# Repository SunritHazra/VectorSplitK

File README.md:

# VectorSplitK

An open-source, wireless, high-profile 42-key mechanical split keyboard. Built around the powerful Seeed Studio XIAO nRF52840, the VectorSplitK features an aggressive columnar stagger, custom-modeled flat profile keycaps, and a robust dual-case mechanical assembly. This project is my first split keyboard. The PCB was made entirely in KiCad and the CAD was done in Autodesk Fusion.

> Full day-by-day design log, decisions, and dead ends: [JOURNAL.md](./JOURNAL.md)

**Project stats:** 14 build-log days · ~40h 20m total design time · 100% designing progress, 0% building progress (as of the latest journal entry)

**On the name:** Follows the author's personal naming convention for electronics projects (used previously for *hackpad* and *devboard*) — a descriptive word, a short form of the project's defining trait ("Split"), and a single trailing letter — giving **VectorSplitK**.

---

## Renders

### Standard Top View

### Isometric Split Profile

### Rear Profile (USB-C & Alignment)

---

## Hardware Architecture

### 1. Electrical Schematic

The electrical system uses hierarchical sheets in KiCad to define identical left and right sides. It resolves typical multi-sheet duplicate ground issues by utilizing sheet-specific power flags (${SHEETNAME}_GND).

Main Sheet

Left Half Matrix

Right Half Matrix

### 2. Footprints

- **Switch Footprints:** High-profile `acheron_MXH:MX100H` (1.00u) and `acheron_MXH:MX150H` (1.50u) hotswap-ready switches (42 total, 21 per side).
- **Diodes:** `Diode_SMD:D_SOD-123` (42 total, 1 per key).
- **Mounting Holes:** `MountingHole:MountingHole_3.2mm_M3_DIN965_Pad` (8 total, 4 per side).
- **Resistors:** `Resistor_SMD:R_0805_2012Metric` (4 total, 2 per side).
- **Integrated Circuit:** `modified-XIAO-nRF52840-SMD:modified-XIAO-nRF52840-SMD` (2 total, 1 per side).
- **Testing Points:** `TestPoint:TestPoint_Pad_D2.0mm` (4 total, 2 per side).
- **Mousebites:** Clean PCB snapping using `PCM_marbastlib-various:mousebites_5p5mm_easysnap` (3 break-offs).

### 3. Printed Circuit Board Assembly

Designed for rugged reliability and high-profile ergonomics using the custom footprints above.

KiCad PCB Window

KiCad PCB Render

KiCad PCBA Render

KiCad PCB Back Side

KiCad PCBA Back Side

- **Design files:** [`/PCBA`](./PCBA)

### 4. Enclosure & CAD Assembly

Designed from scratch in Autodesk Fusion, featuring integrated battery slots, precise USB-C ports, and secure brass threaded insert sockets.

file structure of fusion

top case and bottom case together in fusion

section analysis in fusion showing the screw assembly

- **Tolerance Offset:** 0.2 mm case-on-case fit alignment.
- **Plates:** Structural upper case acts as a switch plate, anchoring switches securely.
- **Keycaps:** Custom-modeled 1.00u and 1.50u flat profile MX-stem keycaps tailored for 3D printing.
- **CAD files:** [`/CAD`](./CAD)

---

## Libraries & References

**KiCad libraries used:**
- [mito-keyboard](https://github.com/mito-keyboard/sito-simplified/tree/sain) — base keyboard library
- [marbastlib](https://github.com/ebastler/marbastlib) — mousebite & hardware footprints
- [Panelization](https://github.com/madworm/Panelization.pretty) — panelization footprints
- [Seeed XIAO KiCad Library](https://github.com/Seeed-Studio/OPL_Kicad_Library/blob/master/XIAO%20Family/XIAO.kicad_sch) — XIAO nRF52840 schematic symbol

**Layout & edge-cut inspiration** (referenced for switch arrangement and board outline conventions):
- [mito-keyboard](https://github.com/mito-keyboard/mito-simplified/tree/main)
- [TaoTeChing](https://github.com/sudo-apt-install-tap/TaoTeChing)
- [OVERRIDE-X3D-Split-Keeb](https://github.com/DevX-Dragon/OVERRIDE-X3D-Split-Keeb)

**Keycap reference model:** [Flat MX Keycaps — Printables](https://www.printables.com/model/467351-flat-mx-keycaps), used as a base to project and re-model custom 1.00u/1.50u profiles.

---

## Design Notes

**Columnar stagger layout:** Switches placed on a 20 mm grid; second and fourth rows shifted 10 mm up, the middle row shifted 20 mm up, with board edges drawn 5 mm out from the outermost keys.

**Hierarchical sheet grounding:** KiCad hierarchical sheets duplicate net names by default, which merged the left/right ground nets into one. Fixed using sheet-specific power flags (`${SHEETNAME}_GND`), producing distinct `Left_GND` and `Right_GND` nets per half.

**Case construction (Fusion 360):** Built symmetrically — one side of the PCB modeled, then mirrored — with:
- Screw hubs extruded directly from the PCB's mounting hole positions
- A battery cavity sized to the WLY394058 LiPo and centered relative to the four mounting screws
- A USB-C cutout on the lower case wall, offset slightly oversized for clearance

**Keycap modeling:** 1.00u caps built by lofting projected upper/lower faces of a reference keycap, then hollowing and adding a stem + cross-hub. 1.50u caps were derived by splitting the 1.00u shape, spacing the halves 9 mm apart, and bridging the gap. Stem geometry was verified by cutting the actual switch stem shape directly into the keycap model to guarantee fit.

**Upper case (switch plate):** Modeled by projecting all switch bodies into a sketch, offsetting 1 mm around each switch and 1.5 mm along the walls, then extruding to the wall thickness (4.05 mm) with screw-hole pillars extended up from the PCB. Outer walls were thinned via a −0.8 mm facial offset on the curved edges for a lighter profile. Corner/cutout dimensions (14.70 × 14.70 mm switch openings, 0.705 mm corner radius) were carried over from the author's earlier hackpad build.

**Design refinements:** The SoC position, PCB mounting holes, and upper-case mounting holes were all iterated to (1) clear the USB-C cable path symmetrically on both halves, (2) keep mounting holes equidistant from the three nearest switches for insert clearance, and (3) keep the upper-case screw geometry in sync with the final PCB layout.

---

## Fabrication & Testing

- **Electrical Rule Check (ERC)** run after schematic completion to catch connection errors before layout.
- **Design Rule Check (DRC)** run after routing, with remaining clearance/edge errors resolved before export.
- **Silkscreen:** Front Fab and Back Fab converted to Back Silkscreen; User.Drawings converted to Front Silkscreen and User.Eco1 to Back Silkscreen; testing points manually labeled and text centered relative to switches. Author name, project name, and build month/year added to the front silkscreen for the final revision.
- **Gerber export:** Full fabrication output exported as `VectorSplitK_Gerber.zip`.
- **Fab test:** Gerbers test-uploaded to JLCPCB to validate manufacturability ahead of ordering.
- **STEP export:** PCB exported at multiple levels of detail (full detail for reference, minimal/simplified for clean CAD import) to support Fusion 360 case modeling.

---

## Bill of Materials (BOM)

Full sourcing sheet with vendors and pricing: [`/Bill of Materials`](<./Bill of Materials>)

### Electronics & PCBs

- **2x** PCBs (Left & Right snap-apart panels)
- **2x** Seeed Studio XIAO nRF52840 MCU boards
- **2x** WLY394058 3.7V 1000mAh 1S LiPo Batteries (3.9 mm thickness for slim fit)
- **42x** Mechanical switches (MX compatible)
- **42x** Kailh MX Hotswap Sockets
- **42x** SOD-123 SMD Diodes (`1N4148`)
- **4x** `0805` Metric SMD Resistors (2 per side)

### Hardware & Case Assembly

- **M3** Screws (Specific lengths to clamp top and bottom cases)
- **M3** Brass Knurled Heat-Staking Inserts (Pressed into bottom case pillars)
- **1x Set** Custom-printed 1.00u & 1.50u flat keycaps (STEP files included)

### Sourcing

| Component | Vendor |
|---|---|
| PCB Fabrication | JLCPCB |
| Switches & Kailh Hotswap Sockets | Meckeys |
| Diodes, Resistors, SoC, Battery | Robu.in |
| Screws & Knurled Inserts | OnlyScrews |

---

## Firmware

The board runs wireless **ZMK** firmware on the **XIAO nRF52840**, using a custom shield built on the upstream `seeeduino_xiao_ble` board support.

### Matrix

5 columns × 5 rows per half (21 keys/side, 42 total — a 4×5 grid plus 1 thumb key), with `diode-direction = "col2row"` matching the SOD-123 diode orientation on the PCB.

| Signal | XIAO Pin |
|---|---|
| COL_0 | P0.03 |
| COL_1 | P0.28 |
| COL_2 | P0.29 |
| COL_3 | P0.04 |
| COL_4 | P0.05 |
| ROW_0 | P1.15 |
| ROW_1 | P1.14 |
| ROW_2 | P1.13 |
| ROW_3 | P1.12 |
| ROW_4 | P1.11 |

### Config

Firmware lives in [`/zmk-config`](./zmk-config), structured as its own ZMK user-config repo:
zmk-config/
├── build.yaml
├── config/
│   ├── vectorsplitk.keymap
│   ├── vectorsplitk.conf
│   └── west.yml
├── boards/shields/vectorsplitk/
│   ├── vectorsplitk.dtsi
│   ├── vectorsplitk_left.overlay
│   ├── vectorsplitk_right.overlay
│   ├── vectorsplitk.zmk.yml
│   ├── Kconfig.shield
│   └── Kconfig.defconfig
└── .github/workflows/build.yml

Pushing this folder as its own GitHub repo triggers a GitHub Actions build via `build.yaml`, producing `vectorsplitk_left-seeeduino_xiao_ble-zmk.uf2` and `vectorsplitk_right-seeeduino_xiao_ble-zmk.uf2` under the Actions tab, no local toolchain required.

> **Known caveat:** the matrix transform assumes COL_0 is the innermost column (closest to the thumb key) on both halves. If keys type in mirrored left-right order on first flash, reverse the column order in `vectorsplitk.dtsi` — a firmware-only fix, no rewiring needed.

### Flashing

1. Double-tap Reset on the XIAO nRF52840 to mount it as a USB drive.
2. Drag the matching `.uf2` (left or right) onto the drive.

---

## AI as a Design Collaborator

While the hardware engineering, PCB routing, firmware architecture, and 3D CAD modeling were completed manually, AI (Gemini, ChatGPT, and Claude) was used as a technical assistant throughout the project—not to generate designs, but to help research, troubleshoot, validate decisions, and improve documentation.

- **Brainstorming:** Helped refine the project name (**VectorSplitK**).
- **Research & Validation:** Verified switch footprints, component choices, and battery selection.
- **Debugging:** Assisted in resolving KiCad schematic and hierarchical-sheet issues.
- **Design Review:** Discussed engineering trade-offs, BOM costs, and manufacturing decisions.
- **Firmware & Documentation:** Helped architect the initial ZMK firmware configuration, reviewed the PCB matrix for firmware setup, and improved the project's technical documentation.

> **Project Integrity:** All schematics, PCB layouts, routing, CAD models, and mechanical design were created manually in KiCad and Autodesk Fusion. AI was used only for research, troubleshooting, review, firmware guidance, and documentation.

---

## License

This project is licensed under the MIT License - see the [LICENSE](./LICENSE) file for details.

---

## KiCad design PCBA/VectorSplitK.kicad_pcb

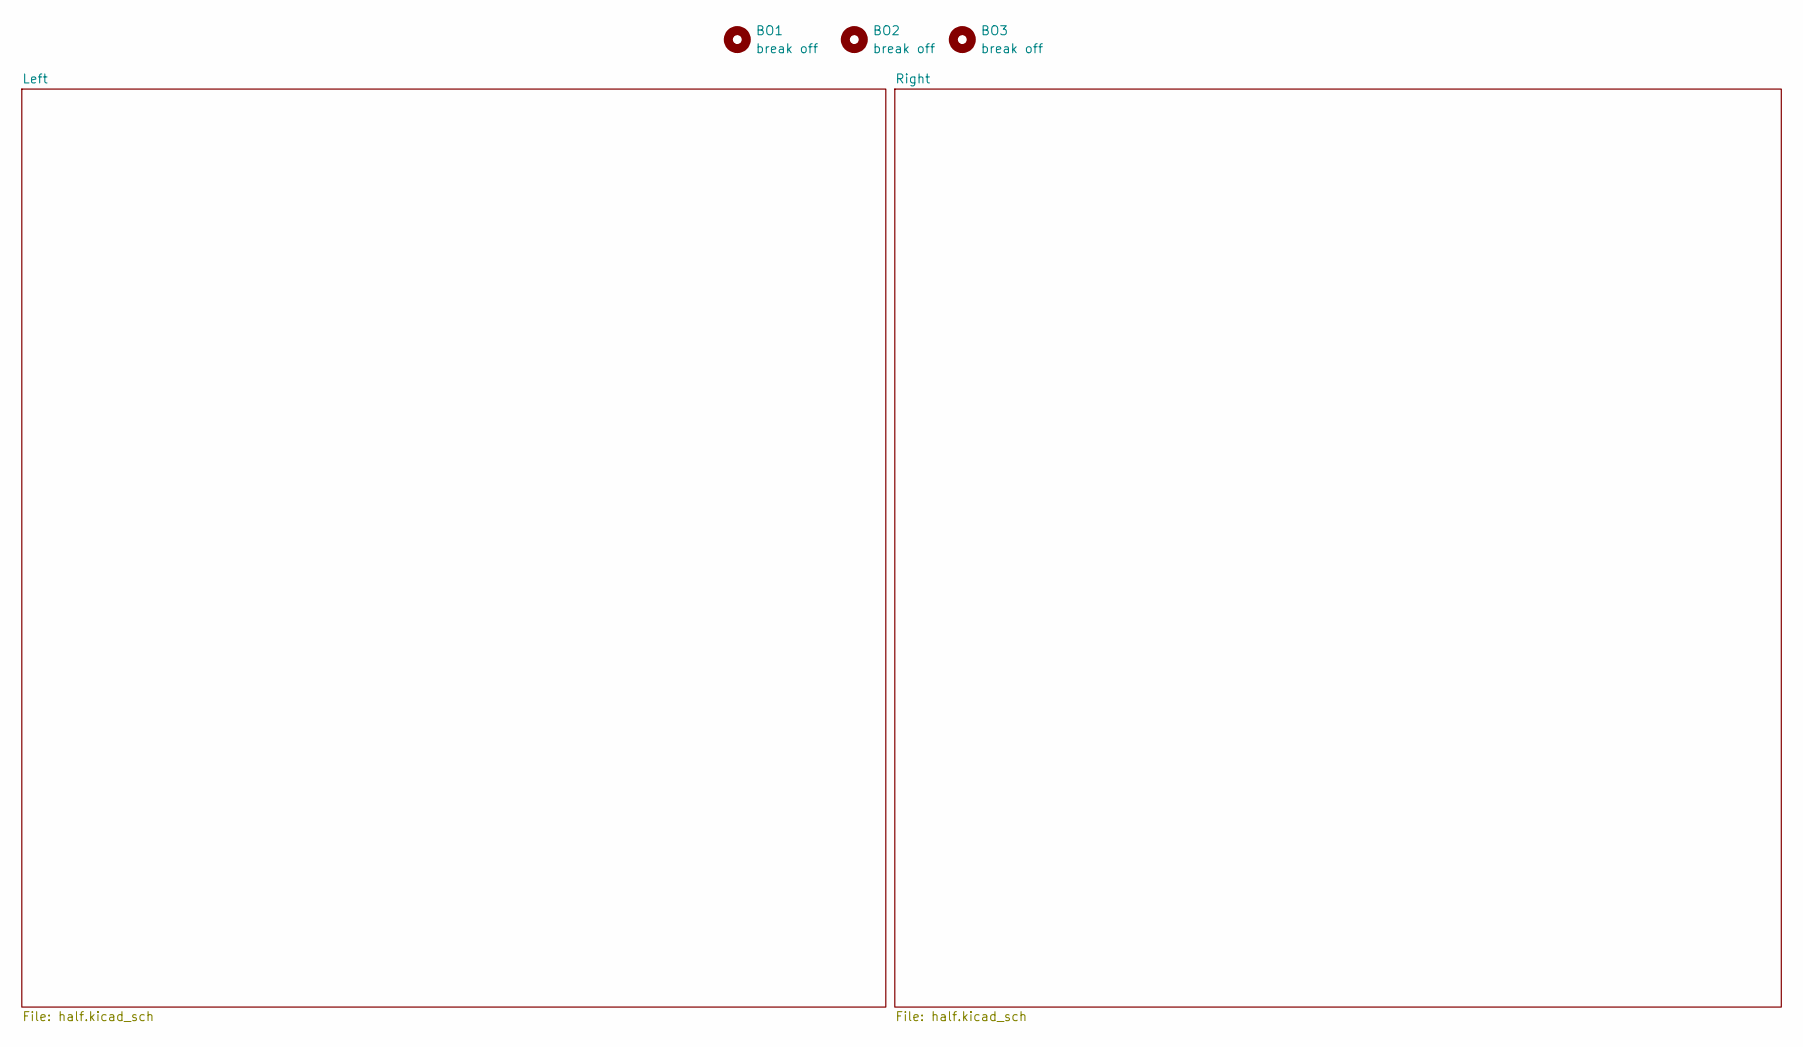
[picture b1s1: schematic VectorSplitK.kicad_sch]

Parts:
BO1, BO2, BO3: break off; mouse-bite-2mm-slot

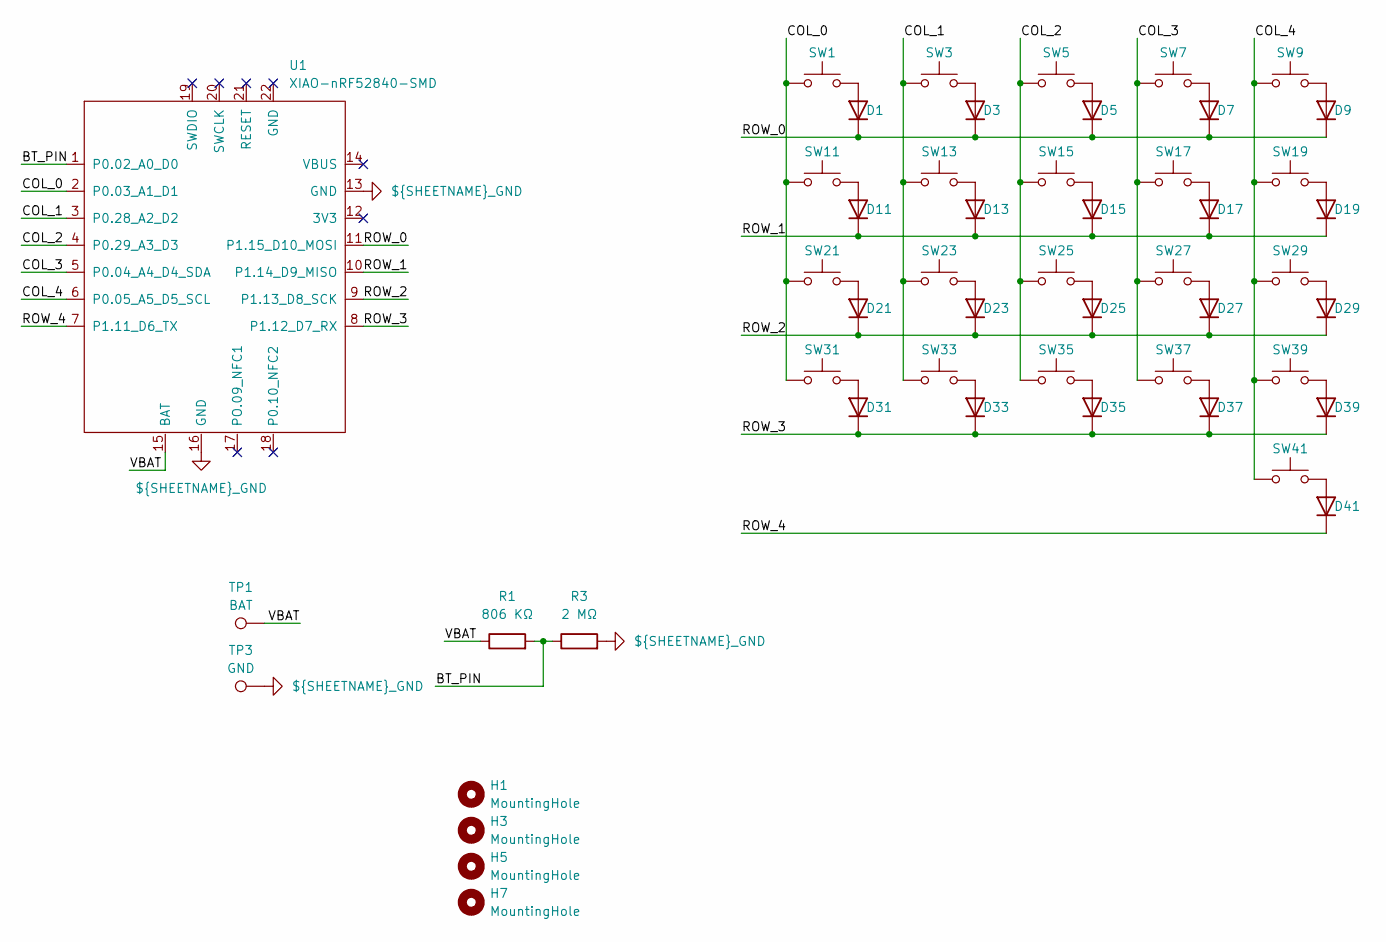
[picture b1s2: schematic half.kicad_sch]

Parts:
D1, D3, D5, D7, D9, D11, D13, D15, D17, D19, D21, D23, D25, D27, D29, D31, D33, D35, D37, D39, D41: D; D_SOD-123
H1, H3, H5, H7: MountingHole; MountingHole_3.2mm_M3_DIN965_Pad
R1: 806 KΩ; R_0805_2012Metric
R3: 2 MΩ; R_0805_2012Metric
SW1, SW3, SW5, SW7, SW9, SW11, SW13, SW15, SW17, SW19, SW21, SW23, SW25, SW27, SW29, SW31, SW33, SW35, SW37, SW39: SW_Push; MX100H
SW41: SW_Push; MX150H
TP1: BAT; TestPoint_Pad_D2.0mm
TP3: GND; TestPoint_Pad_D2.0mm
U1: XIAO-nRF52840-SMD; modified-XIAO-nRF52840-SMD

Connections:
/Left/BT_PIN: R1.2, R3.1, U1.1 (P0.02_A0_D0)
/Left/COL_0: SW1.1, SW11.1, SW21.1, SW31.1, U1.2 (P0.03_A1_D1)
/Left/COL_1: SW3.1, SW13.1, SW23.1, SW33.1, U1.3 (P0.28_A2_D2)
/Left/COL_2: SW5.1, SW15.1, SW25.1, SW35.1, U1.4 (P0.29_A3_D3)
/Left/COL_3: SW7.1, SW17.1, SW27.1, SW37.1, U1.5 (P0.04_A4_D4_SDA)
/Left/COL_4: SW9.1, SW19.1, SW29.1, SW39.1, SW41.1, U1.6 (P0.05_A5_D5_SCL)
/Left/ROW_0: D1.1 (K), D3.1 (K), D5.1 (K), D7.1 (K), D9.1 (K), U1.11 (P1.15_D10_MOSI)
/Left/ROW_1: D11.1 (K), D13.1 (K), D15.1 (K), D17.1 (K), D19.1 (K), U1.10 (P1.14_D9_MISO)
/Left/ROW_2: D21.1 (K), D23.1 (K), D25.1 (K), D27.1 (K), D29.1 (K), U1.9 (P1.13_D8_SCK)
/Left/ROW_3: D31.1 (K), D33.1 (K), D35.1 (K), D37.1 (K), D39.1 (K), U1.8 (P1.12_D7_RX)
/Left/ROW_4: D41.1 (K), U1.7 (P1.11_D6_TX)
/Left/VBAT: R1.1, TP1.1, U1.15 (BAT)
Left_GND: R3.2, TP3.1, U1.13 (GND), U1.16 (GND)
unnamed: D1.2 (A), SW1.2
unnamed: D3.2 (A), SW3.2
unnamed: D5.2 (A), SW5.2
unnamed: D7.2 (A), SW7.2
unnamed: D9.2 (A), SW9.2
unnamed: D11.2 (A), SW11.2
unnamed: D13.2 (A), SW13.2
unnamed: D15.2 (A), SW15.2
unnamed: D17.2 (A), SW17.2
unnamed: D19.2 (A), SW19.2
unnamed: D21.2 (A), SW21.2
unnamed: D23.2 (A), SW23.2
unnamed: D25.2 (A), SW25.2
unnamed: D27.2 (A), SW27.2
unnamed: D29.2 (A), SW29.2
unnamed: D31.2 (A), SW31.2
unnamed: D33.2 (A), SW33.2
unnamed: D35.2 (A), SW35.2
unnamed: D37.2 (A), SW37.2
unnamed: D39.2 (A), SW39.2
unnamed: D41.2 (A), SW41.2

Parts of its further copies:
D2, D4, D6, D8, D10, D12, D14, D16, D18, D20, D22, D24, D26, D28, D30, D32, D34, D36, D38, D40, D42: D; D_SOD-123
H2, H4, H6, H8: MountingHole; MountingHole_3.2mm_M3_DIN965_Pad
R2: 806 KΩ; R_0805_2012Metric
R4: 2 MΩ; R_0805_2012Metric
SW2, SW4, SW6, SW8, SW10, SW12, SW14, SW16, SW18, SW20, SW22, SW24, SW26, SW28, SW30, SW32, SW34, SW36, SW38, SW40: SW_Push; MX100H
SW42: SW_Push; MX150H
TP2: BAT; TestPoint_Pad_D2.0mm
TP4: GND; TestPoint_Pad_D2.0mm
U2: XIAO-nRF52840-SMD; modified-XIAO-nRF52840-SMD

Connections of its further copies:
/Right/BT_PIN: R2.2, R4.1, U2.1 (P0.02_A0_D0)
/Right/COL_0: SW2.1, SW12.1, SW22.1, SW32.1, U2.2 (P0.03_A1_D1)
/Right/COL_1: SW4.1, SW14.1, SW24.1, SW34.1, U2.3 (P0.28_A2_D2)
/Right/COL_2: SW6.1, SW16.1, SW26.1, SW36.1, U2.4 (P0.29_A3_D3)
/Right/COL_3: SW8.1, SW18.1, SW28.1, SW38.1, U2.5 (P0.04_A4_D4_SDA)
/Right/COL_4: SW10.1, SW20.1, SW30.1, SW40.1, SW42.1, U2.6 (P0.05_A5_D5_SCL)
/Right/ROW_0: D2.1 (K), D4.1 (K), D6.1 (K), D8.1 (K), D10.1 (K), U2.11 (P1.15_D10_MOSI)
/Right/ROW_1: D12.1 (K), D14.1 (K), D16.1 (K), D18.1 (K), D20.1 (K), U2.10 (P1.14_D9_MISO)
/Right/ROW_2: D22.1 (K), D24.1 (K), D26.1 (K), D28.1 (K), D30.1 (K), U2.9 (P1.13_D8_SCK)
/Right/ROW_3: D32.1 (K), D34.1 (K), D36.1 (K), D38.1 (K), D40.1 (K), U2.8 (P1.12_D7_RX)
/Right/ROW_4: D42.1 (K), U2.7 (P1.11_D6_TX)
/Right/VBAT: R2.1, TP2.1, U2.15 (BAT)
unnamed: D2.2 (A), SW2.2
unnamed: D4.2 (A), SW4.2
unnamed: D6.2 (A), SW6.2
unnamed: D8.2 (A), SW8.2
unnamed: D10.2 (A), SW10.2
unnamed: D12.2 (A), SW12.2
unnamed: D14.2 (A), SW14.2
unnamed: D16.2 (A), SW16.2
unnamed: D18.2 (A), SW18.2
unnamed: D20.2 (A), SW20.2
unnamed: D22.2 (A), SW22.2
unnamed: D24.2 (A), SW24.2
unnamed: D26.2 (A), SW26.2
unnamed: D28.2 (A), SW28.2
unnamed: D30.2 (A), SW30.2
unnamed: D32.2 (A), SW32.2
unnamed: D34.2 (A), SW34.2
unnamed: D36.2 (A), SW36.2
unnamed: D38.2 (A), SW38.2
unnamed: D40.2 (A), SW40.2
unnamed: D42.2 (A), SW42.2
Right_GND: R4.2, TP4.1, U2.13 (GND), U2.16 (GND)

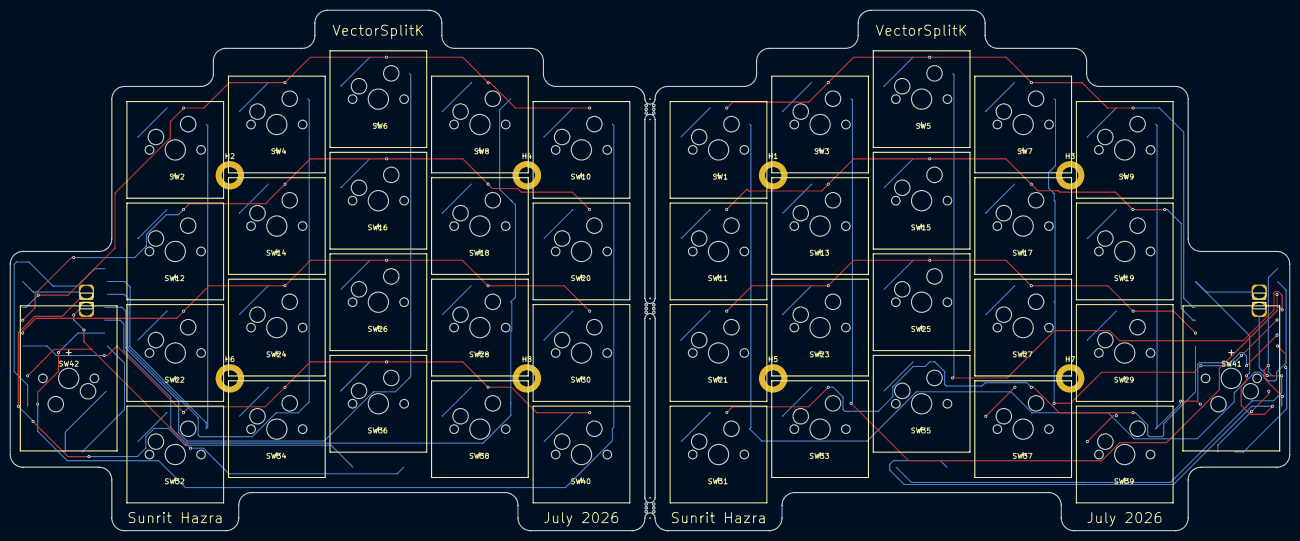
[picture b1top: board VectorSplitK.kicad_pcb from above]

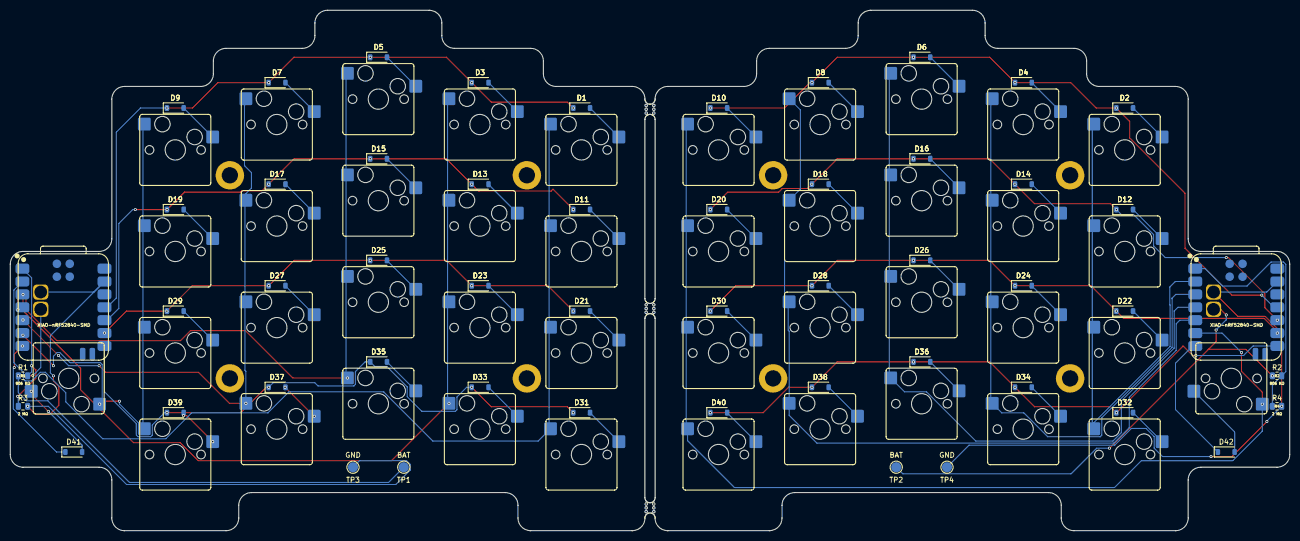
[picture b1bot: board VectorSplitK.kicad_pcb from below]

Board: 2 copper layers, 252.0 x 102.5 mm, 105 parts (97 on the bottom side), 68 nets.
